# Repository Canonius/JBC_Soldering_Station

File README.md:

# JBC_Soldering_Station
Dual JBC T245 compatible 300W soldering station

For quick overview:
https://github.com/Canonius/JBC_Soldering_Station/blob/master/Hardware/Schematic.pdf

SW is added. 
It uses the SSD1306ASCII Library from greiman
https://github.com/greiman/SSD1306Ascii

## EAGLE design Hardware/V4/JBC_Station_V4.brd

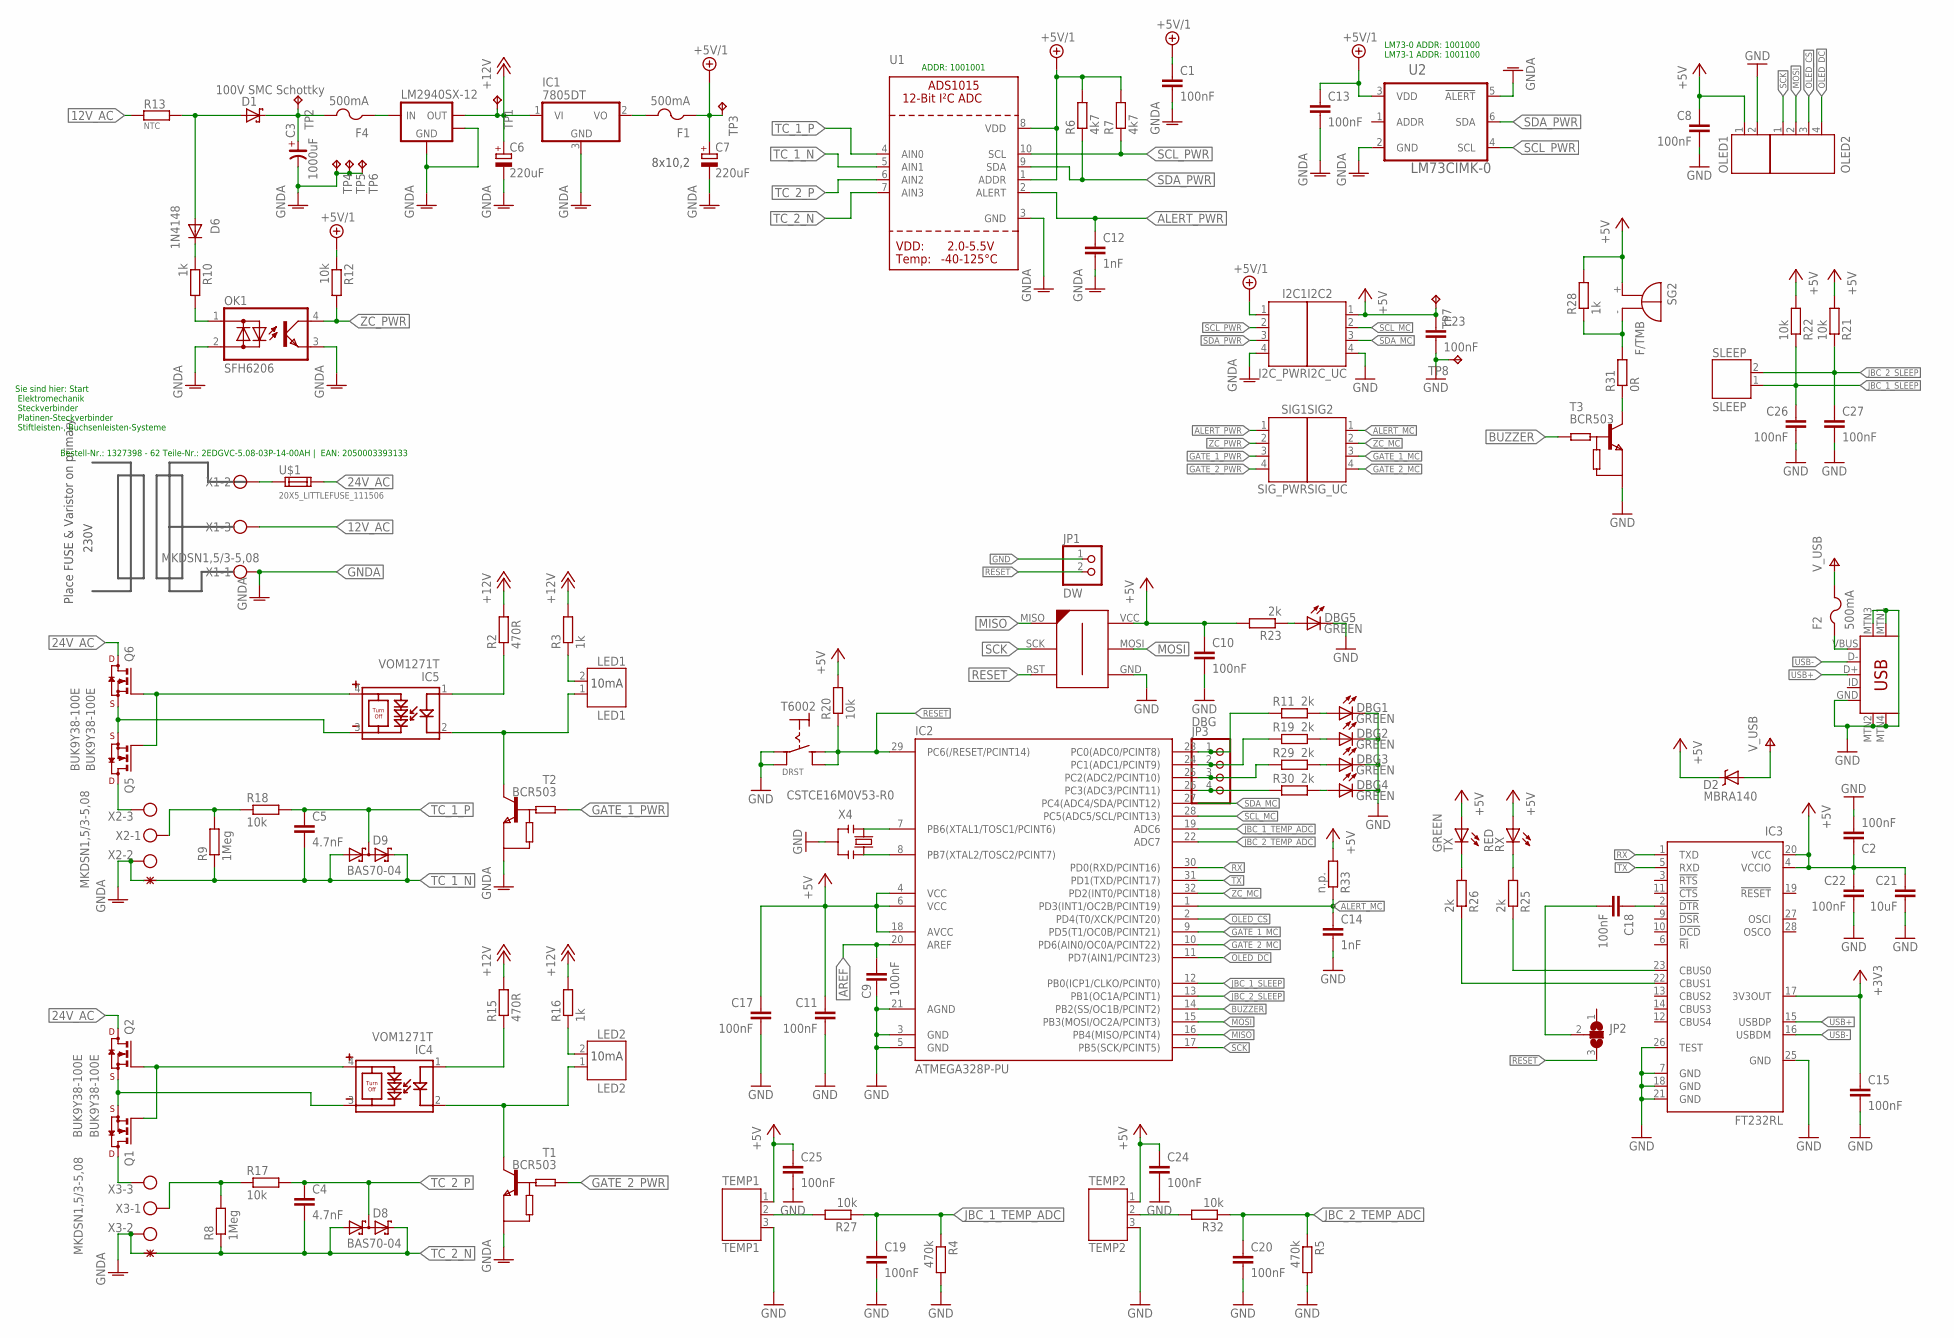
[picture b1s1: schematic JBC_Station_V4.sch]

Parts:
C1, C2, C8, C9, C10, C11, C13, C15, C17, C18, C19, C20, C22, C23, C24, C25, C26, C27: 100nF; C0805
C3: 1000uF; CSV-H
C4, C5: 4.7nF; C0805
C6, C7: 220uF; PANASONIC_E
C12, C14: 1nF; C0805
C21: 10uF; C1210
D1: 100V SMC Schottky; SMC
D2: MBRA140; SMA-DIODE
D6: 1N4148; MINIMELF
D8, D9: BAS70-04; SOT23
DBG1, DBG2, DBG3, DBG4, DBG5: GREEN; CHIP-LED0603
F1, F2, F4: 500mA; R1206
I2C1: I2C_PWR; JST-PH4
I2C2: I2C_UC; JST-PH4
IC1: 7805DT; TO252
IC2: ATMEGA328P-PU; TQFP32-08
IC3: FT232RL; SSOP28
IC4, IC5: VOM1271T; SOP-4
JP1: DW; 1X02
JP2: SJ2W; SJ_2
JP3: DBG; 1X04/90
LED1: LED1; JST-PH2
LED2: LED2; JST-PH2
LM2940SX-12: LM2940KTT; TO263-3
OK1: SFH6206; DIL4-SMD
OLED1: JST-PH2
OLED2: JST-PH4
Q1, Q2, Q5, Q6: BUK9Y38-100E; SOT669-POWERPAK-SO-8L-SINGLE
R2, R15: 470R; R0805
R3, R10, R16, R28: 1k; R0805
R4, R5: 470k; R0805
R6, R7: 4k7; R0805
R8, R9: 1Meg; R0805
R11, R19, R23, R25, R26, R29, R30: 2k; R0805
R12, R17, R18, R20, R21, R22, R27, R32: 10k; R0805
R13: NTC; SQM-VERTICAL-7W
R31: 0R; R0805
R33: n.p.; R0805
RX: RED; CHIP-LED0603
SG2: F/TMB
SIG1: SIG_PWR; JST-PH4
SIG2: SIG_UC; JST-PH4
SLEEP: SLEEP; JST-PH2
T1, T2, T3: BCR503; GM4_BIP_SOT23_RZ
T6002: DRST; TASTE_DRST_TA1
TEMP1: TEMP1; JST-PH3
TEMP2: TEMP2; JST-PH3
TP1, TP2, TP3, TP4, TP5, TP6, TP7, TP8: TPTP17R; TP17R
TX: GREEN; CHIP-LED0603
U1: ADC_ADS1015; MSOP10
U2: LM73CIMK-0; SOT95P285X100-6N
U$1: 20X5_LITTLEFUSE_111506
U$2, U$3: STARPONT; STARPOINT
U$5: AVR-ISP-6-EDGE; 6PAD_ISP
USB: USB-MINIB-5PIN; USB-MINIB
X1, X2, X3: MKDSN1,5/3-5,08
X4: CSTCE16M0V53-R0; RESONATOR

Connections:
12V_AC: R13.P$1 (1), X1.3
12V_AC_PROT: D1.A, D6.A, R13.P$2 (2)
24V_AC: Q2.5 (D), Q6.5 (D), U$1.21 (2), U$1.22 (2)
+3V3: C15.1, IC3.17 (3V3OUT)
+5V: C2.1, C8.1, C10.1, C11.1, C17.1, C21.1, C22.1, C23.1, C24.1, C25.1, D2.C, I2C2.1, IC2.4 (VCC), IC2.6 (VCC), IC2.18 (AVCC), IC3.4 (VCCIO), IC3.20 (VCC), OLED1.1, R20.2, R21.2, R22.2, R23.2, R28.2, R33.2, RX.A, SG2.+, TEMP1.1, TEMP2.1, TP7.TP, TX.A, U$5.VCC
+5V/1: C1.1, C7.+, C13.1, F1.1, I2C1.1, R6.2, R7.2, R12.1, TP3.TP, U1.1 (ADDR), U1.8 (VDD), U2.3 (VDD)
+12V: C6.+, IC1.1 (VI), LM2940SX-12.3 (VOUT), R2.2, R3.2, R15.2, R16.2, TP1.TP
ALERT_MC: C14.1, IC2.1 (PD3(INT1/OC2B/PCINT19)), R33.1, SIG2.1
ALERT_PWR: C12.1, SIG1.1, U1.2 (ALERT)
AREF: C9.1, IC2.20 (AREF)
BUZZER: IC2.14 (PB2(SS/OC1B/PCINT2)), T3.1 (B)
DBG1: IC2.23 (PC0(ADC0/PCINT8)), JP3.1, R11.2
DBG2: IC2.24 (PC1(ADC1/PCINT9)), JP3.2, R19.2
DBG3: IC2.25 (PC2(ADC2/PCINT10)), JP3.3, R29.2
DBG4: IC2.26 (PC3(ADC3/PCINT11)), JP3.4, R30.2
GATE_1_MC: IC2.9 (PD5(T1/OC0B/PCINT21)), SIG2.3
GATE_1_PWR: SIG1.3, T2.1 (B)
GATE_2_MC: IC2.10 (PD6(AIN0/OC0A/PCINT22)), SIG2.4
GATE_2_PWR: SIG1.4, T1.1 (B)
GND: C2.2, C8.2, C9.2, C10.2, C11.2, C14.2, C15.2, C17.2, C19.2, C20.2, C21.2, C22.2, C23.2, C24.2, C25.2, C26.2, C27.2, DBG1.C, DBG2.C, DBG3.C, DBG4.C, DBG5.C, I2C2.4, IC2.3 (GND), IC2.5 (GND), IC2.21 (AGND), IC3.7 (GND), IC3.18 (GND), IC3.21 (GND), IC3.25 (GND), IC3.26 (TEST), JP1.1, OLED1.2, R4.2, R5.2, T3.2 (E), T6002.P$1 (1), T6002.P$2 (1), TEMP1.3, TEMP2.3, TP8.TP, U$5.GND, USB.GND, USB.MTN1 (MTN2), USB.MTN2 (MTN3), USB.MTN3 (MTN1), USB.MTN4, X4.2
GNDA: C1.2, C3.-, C6.-, C7.-, C12.2, C13.2, I2C1.4, IC1.3 (GND), LM2940SX-12.2 (GND), LM2940SX-12.TAB, OK1.2 (AC2), OK1.3 (E), T1.2 (E), T2.2 (E), TP4.TP, TP5.TP, TP6.TP, U1.3 (GND), U2.2 (GND), U2.5 (!ALERT!), U$2.P$2, U$3.P$2, X1.1, X2.2, X3.2
JBC_1_SLEEP: C26.1, IC2.12 (PB0(ICP1/CLKO/PCINT0)), R22.1, SLEEP.1
JBC_1_TEMP_ADC: C19.1, IC2.19 (ADC6), R4.1, R27.1
JBC_2_SLEEP: C27.1, IC2.13 (PB1(OC1A/PCINT1)), R21.1, SLEEP.2
JBC_2_TEMP_ADC: C20.1, IC2.22 (ADC7), R5.1, R32.1
MISO: IC2.16 (PB4(MISO/PCINT4)), U$5.MISO
MOSI: IC2.15 (PB3(MOSI/OC2A/PCINT3)), OLED2.2, U$5.MOSI
unnamed: IC5.4, Q5.4 (G), Q6.4 (G)
unnamed: LED1.2, R3.1
unnamed: IC5.2, LED1.1, T2.3 (C)
unnamed: IC5.1, R2.1
unnamed: IC2.7 (PB6(XTAL1/TOSC1/PCINT6)), X4.1
unnamed: IC4.4, Q1.4 (G), Q2.4 (G)
unnamed: Q5.5 (D), X2.3
unnamed: OK1.1 (AC1), R10.2
unnamed: Q1.5 (D), X3.3
unnamed: R9.2, R18.1, X2.1
unnamed: C3.+, D1.C, F4.2, TP2.TP
unnamed: R8.2, R17.1, X3.1
unnamed: IC5.3, Q5.1 (S), Q5.2 (S), Q5.3 (S), Q6.1 (S), Q6.2 (S), Q6.3 (S)
unnamed: IC4.3, Q1.1 (S), Q1.2 (S), Q1.3 (S), Q2.1 (S), Q2.2 (S), Q2.3 (S)
unnamed: IC4.2, LED2.1, T1.3 (C)
unnamed: IC4.1, R15.1
unnamed: IC2.8 (PB7(XTAL2/TOSC2/PCINT7)), X4.3
unnamed: LED2.2, R16.1
unnamed: U$1.11 (1), U$1.12 (1), X1.2
unnamed: D6.C, R10.1
unnamed: C18.2, JP2.2
unnamed: C18.1, IC3.2 (!DTR)
unnamed: F1.2, IC1.2 (VO)
unnamed: DBG5.A, R23.1
unnamed: IC3.23 (CBUS0), R25.1
unnamed: IC3.22 (CBUS1), R26.1
unnamed: R25.2, RX.C
unnamed: F2.1, USB.VBUS
unnamed: R26.2, TX.C
unnamed: R27.2, TEMP1.2
unnamed: R28.1, R31.2, SG2.-
unnamed: DBG1.A, R11.1
unnamed: F4.1, LM2940SX-12.1 (VIN)
unnamed: DBG2.A, R19.1
unnamed: DBG3.A, R29.1
unnamed: DBG4.A, R30.1
unnamed: R31.1, T3.3 (C)
unnamed: R32.2, TEMP2.2
OLED_CS: IC2.2 (PD4(T0/XCK/PCINT20)), OLED2.3
OLED_DC: IC2.11 (PD7(AIN1/PCINT23)), OLED2.4
RESET: IC2.29 (PC6(/RESET/PCINT14)), JP1.2, JP2.3, R20.1, T6002.P$3 (2), T6002.P$4 (2), U$5.RST
RX: IC2.30 (PD0(RXD/PCINT16)), IC3.1 (TXD)
SCK: IC2.17 (PB5(SCK/PCINT5)), OLED2.1, U$5.SCK
SCL_MC: I2C2.2, IC2.28 (PC5(ADC5/SCL/PCINT13))
SCL_PWR: I2C1.2, R7.1, U1.10 (SCL), U2.4 (SCL)
SDA_MC: I2C2.3, IC2.27 (PC4(ADC4/SDA/PCINT12))
SDA_PWR: I2C1.3, R6.1, U1.9 (SDA), U2.6 (SDA)
TC_1_N: C5.2, D9.1 (A1), D9.2 (C2), R9.1, U1.5 (AIN1), U$2.P$1
TC_1_P: C5.1, D9.3 (C1A2), R18.2, U1.4 (AIN0)
TC_2_N: C4.2, D8.1 (A1), D8.2 (C2), R8.1, U1.7 (AIN3), U$3.P$1
TC_2_P: C4.1, D8.3 (C1A2), R17.2, U1.6 (AIN2)
TX: IC2.31 (PD1(TXD/PCINT17)), IC3.5 (RXD)
USB+: IC3.15 (USBDP), USB.D+
USB-: IC3.16 (USBDM), USB.D-
V+: D2.A, F2.2
ZC_MC: IC2.32 (PD2(INT0/PCINT18)), SIG2.2
ZC_PWR: OK1.4 (C), R12.2, SIG1.2

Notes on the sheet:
230V
8x10,2
ADDR: 1001001
LM73-0 ADDR: 1001000 LM73-1 ADDR: 1001100
Bestell-Nr.: 1327398 - 62 Teile-Nr.: 2EDGVC-5.08-03P-14-00AH | EAN: 2050003393133
Sie sind hier: Start Elektromechanik Steckverbinder Platinen-Steckverbinder Stiftleisten-, Buchsenleisten-Systeme
10mA
Place FUSE & Varistor on primary

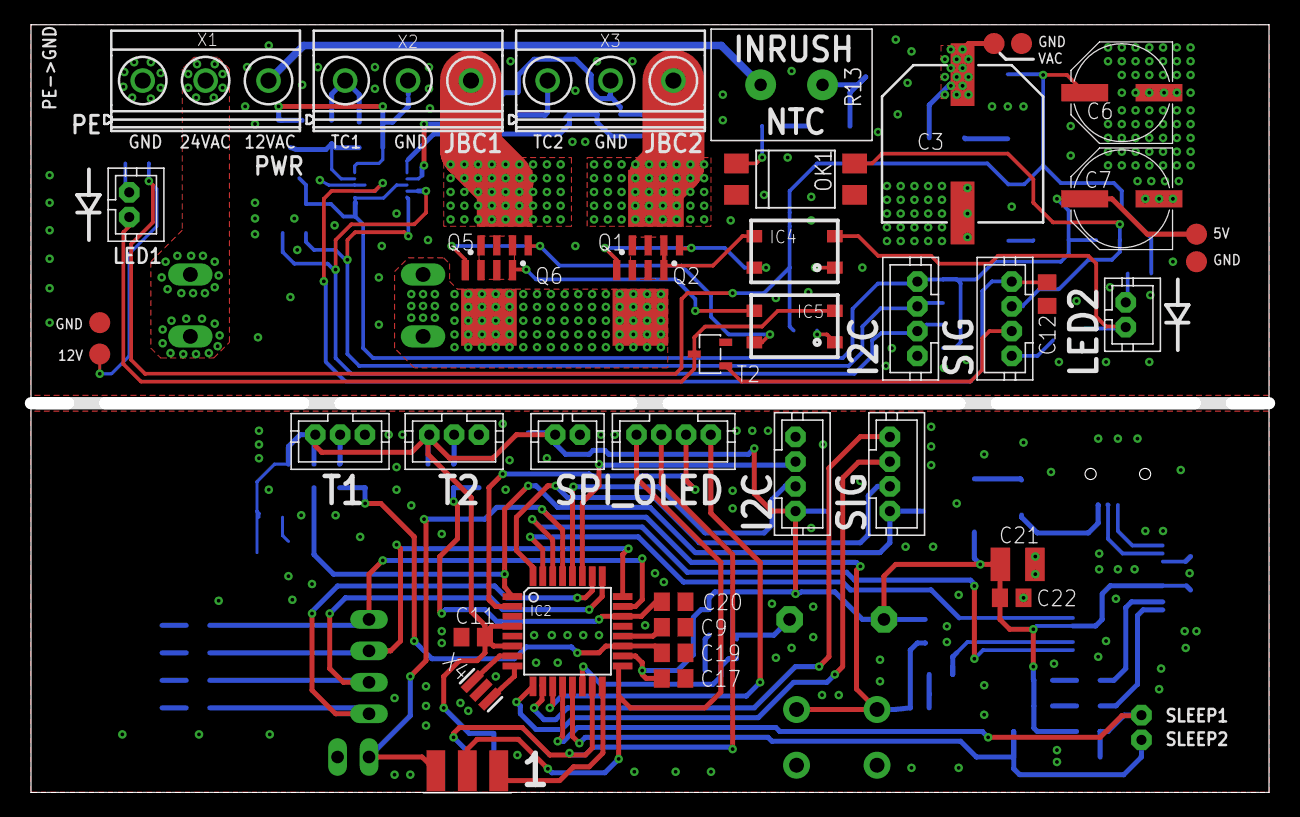
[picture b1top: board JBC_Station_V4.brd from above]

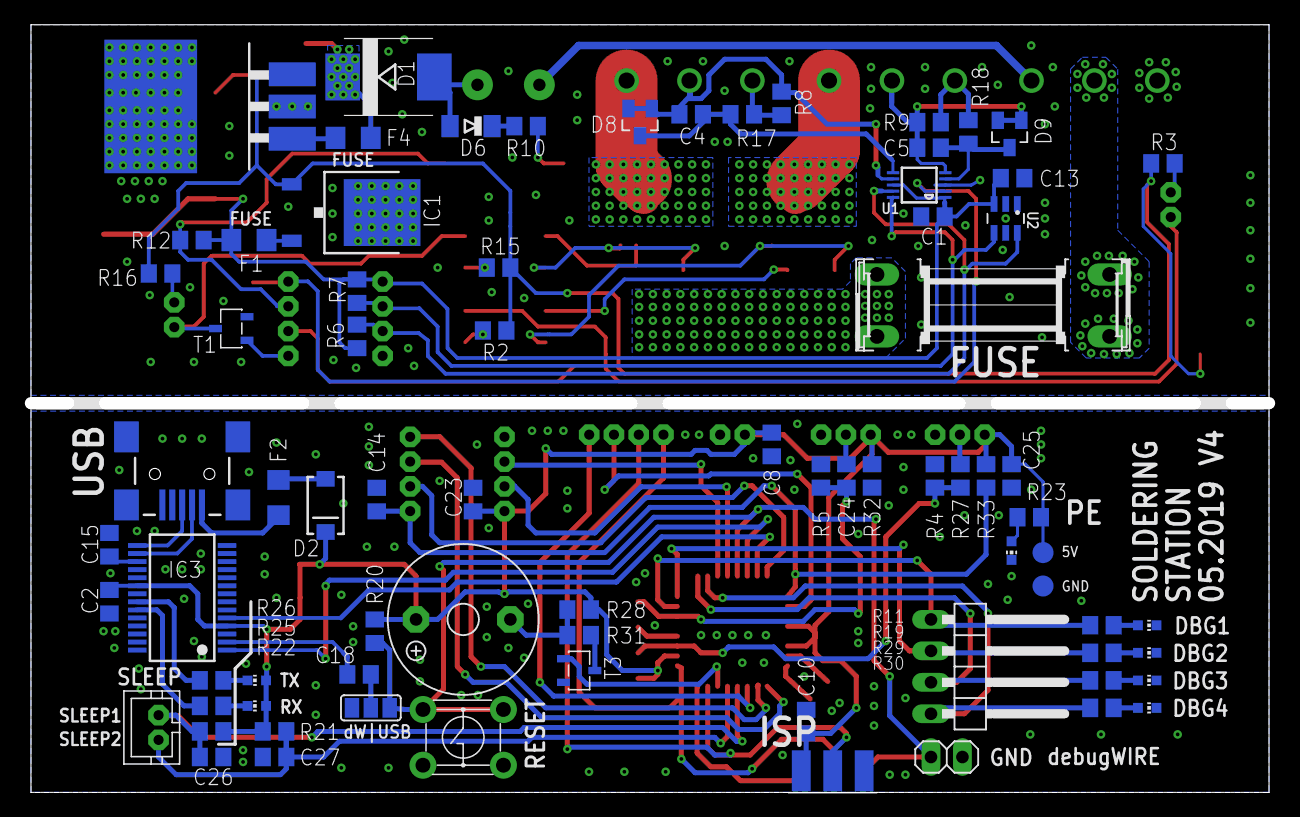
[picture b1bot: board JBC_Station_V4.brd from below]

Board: 2 copper layers, 100.0 x 61.0 mm, 120 parts (78 on the bottom side), 84 nets.

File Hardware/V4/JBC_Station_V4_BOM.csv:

"Qty";"Value";"Device";"Package";"Parts";"Description";"CASE";"MF";"MONTHLY_USAGE";"MPN";"OC_FARNELL";"OC_NEWARK";"PACKAGE";"PART_NUMBER";"PRICE";"SUPPLIER";"TP_SIGNAL_NAME";"TYPE";"VALUE";"_EXTERNAL_";
"1";"ADS1115";"ADC_ADS1015";"MSOP10";"U1";"ADS1015 - 12-bit 4-Channel I2C ADC with Internal PGA";"";"";"";"";"";"";"";"";"";"";"";"";"";"";
"1";"";"JST-PH2";"JST-PH2";"OLED1";"";"";"";"";"";"";"";"";"";"";"";"";"";"";"";
"1";"";"JST-PH4";"JST-PH4";"OLED2";"";"";"";"";"";"";"";"";"";"";"";"";"";"";"";
"1";"";"LM2940KTT";"TO263-3";"LM2940SX-12";"LM2940 LDO Voltage Regulator";"";"";"";"";"";"";"";"";"";"";"";"";"";"";
"1";"";"SJ2W";"SJ_2";"JP2";"SMD solder JUMPER";"";"";"";"";"";"";"";"";"";"";"";"";"";"";
"1";"0R";"R-EU_R0805";"R0805";"R31";"RESISTOR, European symbol";"";"";"";"";"";"";"";"";"";"";"";"";"";"";
"1";"1000uF";"CP_SV-H";"CSV-H";"C3";"POLARIZED CAP";"";"";"";"";"";"";"";"";"";"";"";"";"";"";
"1";"100V SMC Schottky";"SCHOTTKY-DIODESMC";"SMC";"D1";"Schottky Diode";"";"";"";"";"";"";"";"";"";"";"";"";"";"";
"18";"100nF";"C-EUC0805";"C0805";"C1, C2, C8, C9, C10, C11, C13, C15, C17, C18, C19, C20, C22, C23, C24, C25, C26, C27";"CAPACITOR, European symbol";"";"";"";"";"";"";"";"";"";"";"";"";"";"";
"8";"10k";"R-EU_R0805";"R0805";"R12, R17, R18, R20, R21, R22, R27, R32";"RESISTOR, European symbol";"";"";"";"";"";"";"";"";"";"";"";"";"";"";
"1";"10uF";"C-EUC1210";"C1210";"C21";"CAPACITOR, European symbol";"";"";"";"";"";"";"";"";"";"";"";"";"";"";
"2";"1Meg";"R-EU_R0805";"R0805";"R8, R9";"RESISTOR, European symbol";"";"";"";"";"";"";"";"";"";"";"";"";"";"";
"1";"1N4148";"DIODE-MINIMELF";"MINIMELF";"D6";"DIODE";"";"";"";"";"";"";"";"";"";"";"";"";"";"";
"4";"1k";"R-EU_R0805";"R0805";"R3, R10, R16, R28";"RESISTOR, European symbol";"";"";"";"";"";"";"";"";"";"";"";"";"";"";
"2";"1nF";"C-EUC0805";"C0805";"C12, C14";"CAPACITOR, European symbol";"";"";"";"";"";"";"";"";"";"";"";"";"";"";
"1";"20X5_LITTLEFUSE_111506";"20X5_LITTLEFUSE_111506";"20X5_LITTLEFUSE_111506";"U$1";"Littlefuse 111 506";"";"";"";"";"";"";"";"";"";"";"";"";"";"";
"2";"220uF";"CPOL-EUE";"PANASONIC_E";"C6, C7";"POLARIZED CAPACITOR, European symbol";"";"";"";"";"";"";"";"";"";"";"";"";"";"";
"7";"2k";"R-EU_R0805";"R0805";"R11, R19, R23, R25, R26, R29, R30";"RESISTOR, European symbol";"";"";"";"";"";"";"";"";"";"";"";"";"";"";
"2";"4.7nF";"C-EUC0805";"C0805";"C4, C5";"CAPACITOR, European symbol";"";"";"";"";"";"";"";"";"";"";"";"";"";"";
"2";"470R";"R-EU_R0805";"R0805";"R2, R15";"RESISTOR, European symbol";"";"";"";"";"";"";"";"";"";"";"";"";"";"";
"2";"470k";"R-EU_R0805";"R0805";"R4, R5";"RESISTOR, European symbol";"";"";"";"";"";"";"";"";"";"";"";"";"";"";
"2";"4k7";"R-EU_R0805";"R0805";"R6, R7";"RESISTOR, European symbol";"";"";"";"";"";"";"";"";"";"";"";"";"";"";
"3";"500mA";"PTCFUSE-1206";"R1206";"F1, F2, F4";"PTC fuses, resettable thermistors";"";"";"";"";"";"";"";"";"";"";"";"";"";"";
"1";"7805DT";"7805DT";"TO252";"IC1";"Positive VOLTAGE REGULATOR";"";"";"";"";"";"";"";"";"";"";"";"";"";"";
"1";"ATMEGA328P-PU";"MEGA48/88/168-AU";"TQFP32-08";"IC2";"";"";"";"";"";"";"";"";"";"";"";"";"";"";"";
"1";"AVR-ISP-6-EDGE";"AVR-ISP-6-EDGE";"6PAD_ISP";"U$5";"6 pin edge connector for ISP with ATMEL MCUs.";"";"";"";"";"";"";"";"";"";"";"";"";"";"";
"2";"BAS70-04";"BAS70-04";"SOT23";"D8, D9";"Silicon Schottky Diodes";"";"";"";"";"";"";"";"";"";"";"";"";"";"";
"3";"BCR503";"GM4_BIP_NPN-DIG_SOT23_RZ";"GM4_BIP_SOT23_RZ";"T1, T2, T3";"NPN Digitaltransistor wie BCR148";"";"";"";"";"";"";"";"";"";"";"";"";"";"";
"4";"BUK9Y38-100E";"BUK9Y38-100E";"SOT669-POWERPAK-SO-8L-SINGLE";"Q1, Q2, Q5, Q6";"Alternative Package Names:";"";"";"";"";"";"";"";"";"";"";"";"";"";"";
"1";"CSTCE16M0V53-R0";"0011_CSTCE16M0V53-R0";"RESONATOR";"X4";"16Mhz - SMD";"";"";"_____";"";"";"";"";"CSTCE16M0V53-R0";"_____";"_____";"";"Cristalli";"CSTCE16M0V53-R0";"";
"1";"DBG";"PINHD-1X4/90";"1X04/90";"JP3";"PIN HEADER";"";"";"";"";"";"";"";"";"";"";"";"";"";"";
"1";"DRST";"TASTE_DRST_TA1";"TASTE_DRST_TA1";"T6002";"";"";"";"";"";"";"";"";"";"";"";"";"";"";"";
"1";"DW";"PINHD-1X2_2.54";"1X02";"JP1";"PIN HEADER";"";"";"";"";"";"";"";"";"";"";"";"";"";"";
"1";"F/TMB";"F/TMB";"F/TMB";"SG2";"BUZZER Source: Buerklin";"";"";"";"";"unknown";"unknown";"";"";"";"";"";"";"";"";
"1";"FT232RL";"FT232RL";"SSOP28";"IC3";"Source: http://www.ftdichip.com/Documents/DataSheets/DS_FT232R_v104.pdf";"";"";"";"FT232RL";"1146032";"91K9918";"";"";"";"";"";"";"";"";
"6";"GREEN";"LEDCHIP-LED0603";"CHIP-LED0603";"DBG1, DBG2, DBG3, DBG4, DBG5, TX";"LED";"";"";"";"";"";"";"";"";"";"";"";"";"";"";
"1";"I2C_PWR";"JST-PH4";"JST-PH4";"I2C1";"";"";"";"";"";"";"";"";"";"";"";"";"";"";"";
"1";"I2C_UC";"JST-PH4";"JST-PH4";"I2C2";"";"";"";"";"";"";"";"";"";"";"";"";"";"";"";
"1";"LED1";"JST-PH2";"JST-PH2";"LED1";"";"";"";"";"";"";"";"";"";"";"";"";"";"";"";
"1";"LED2";"JST-PH2";"JST-PH2";"LED2";"";"";"";"";"";"";"";"";"";"";"";"";"";"";"";
"1";"LM73CIMK-0";"LM73CIMK-0";"SOT95P285X100-6N";"U2";"Digital Temperature Sensor";"";"";"";"LM73CIMK-0";"1312598";"69K2606";"SOT-23-6";"";"";"National Semiconductor";"";"";"";"";
"1";"MBRA140";"DIODE-SCHOTTKY_";"SMA-DIODE";"D2";"";"";"";"";"";"";"";"";"";"";"";"";"";"";"";
"3";"MKDSN1,5/3-5,08";"MKDSN1,5/3-5,08";"MKDSN1,5/3-5,08";"X1, X2, X3";"MKDSN 1,5/ 3-5,08 Printklemme";"";"";"";"";"";"";"";"";"";"";"";"";"";"";
"1";"NTC";"SQMR7";"SQM-VERTICAL-7W";"R13";"";"";"";"";"";"";"";"";"";"";"";"";"";"";"";
"1";"RED";"LEDCHIP-LED0603";"CHIP-LED0603";"RX";"LED";"";"";"";"";"";"";"";"";"";"";"";"";"";"";
"1";"SFH6206";"SFH6206";"DIL4-SMD";"OK1";"Optocoupler, Phototransistor Output, AC Input";"";"VISHAY/TELEFUNKEN";"";"SFH6206-3";"1469585";"58K2214";"";"";"";"";"";"";"";"";
"1";"SIG_PWR";"JST-PH4";"JST-PH4";"SIG1";"";"";"";"";"";"";"";"";"";"";"";"";"";"";"";
"1";"SIG_UC";"JST-PH4";"JST-PH4";"SIG2";"";"";"";"";"";"";"";"";"";"";"";"";"";"";"";
"1";"SLEEP";"JST-PH2";"JST-PH2";"SLEEP";"";"";"";"";"";"";"";"";"";"";"";"";"";"";"";
"2";"STARPONT";"STARPONT";"STARPOINT";"U$2, U$3";"";"";"";"";"";"";"";"";"";"";"";"";"";"";"";
"1";"TEMP1";"JST-PH3";"JST-PH3";"TEMP1";"";"";"";"";"";"";"";"";"";"";"";"";"";"";"";
"1";"TEMP2";"JST-PH3";"JST-PH3";"TEMP2";"";"";"";"";"";"";"";"";"";"";"";"";"";"";"";
"8";"TPTP17R";"TPTP17R";"TP17R";"TP1, TP2, TP3, TP4, TP5, TP6, TP7, TP8";"Test pad";"";"";"";"";"";"";"";"";"";"";"";"";"";"";
"1";"USB-MINIB-5PIN";"USB-MINIB-5PIN";"USB-MINIB";"USB";"Mini-USB "B" connector with 5th pin broken out.";"";"";"";"";"";"";"";"";"";"";"";"";"";"";
"2";"VOM1271T";"VOM1271T";"SOP-4";"IC4, IC5";"";"";"";"";"";"";"";"";"";"";"";"";"";"";"";
"1";"n.p.";"R-EU_R0805";"R0805";"R33";"RESISTOR, European symbol";"";"";"";"";"";"";"";"";"";"";"";"";"";"";

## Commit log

2019-07-11 extract in the workspace folder of sloeber
2020-08-30 Add files via upload
    initial upload

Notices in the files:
parts and their libraries:
microbuilder2: This work is placed in the public domain, and may be freely used for commercial and non-commercial work with the following conditions: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
rc-master-smd: Copyright (C) 2007, Bob Starr
SparkFun: Licensing: CC v3.0 Share-Alike You are welcome to use this library for commercial purposes.
